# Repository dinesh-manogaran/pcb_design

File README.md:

View this project on [CADLAB.io](https://cadlab.io/project/29153). 

# pcb_design

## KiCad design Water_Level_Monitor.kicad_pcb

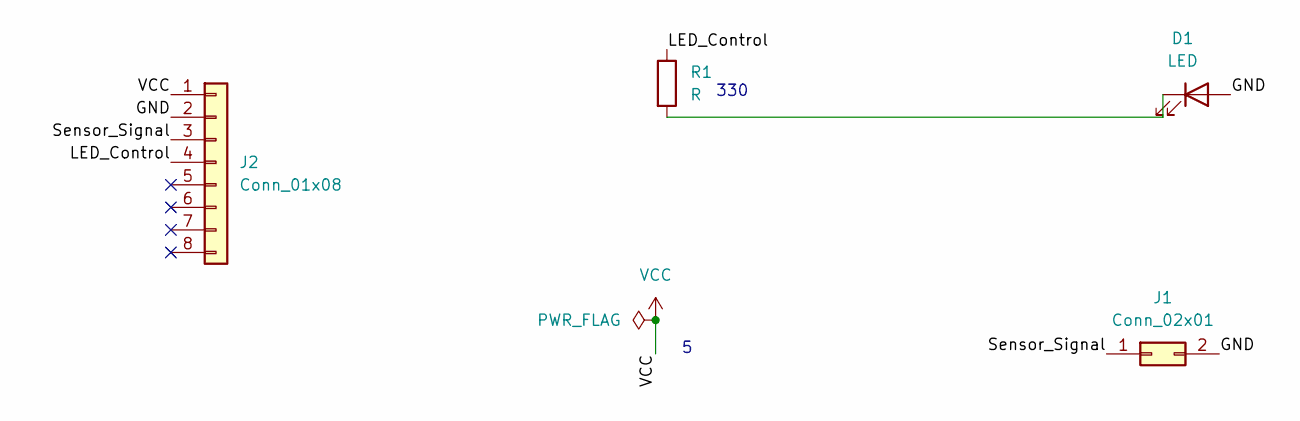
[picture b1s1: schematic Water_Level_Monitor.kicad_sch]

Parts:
D1: LED; LED_D5.0mm
J1: Conn_02x01; PinHeader_1x02_P2.54mm_Vertical
J2: Conn_01x08; PinHeader_1x08_P2.54mm_Vertical
R1: R; R_Axial_DIN0207_L6.3mm_D2.5mm_P7.62mm_Horizontal

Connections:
/GND: D1.2 (A), J1.2, J2.2
/LED_Control: J2.4, R1.1
/Sensor_Signal: J1.1, J2.3
unnamed: D1.1 (K), R1.2
VCC: J2.1

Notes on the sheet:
330

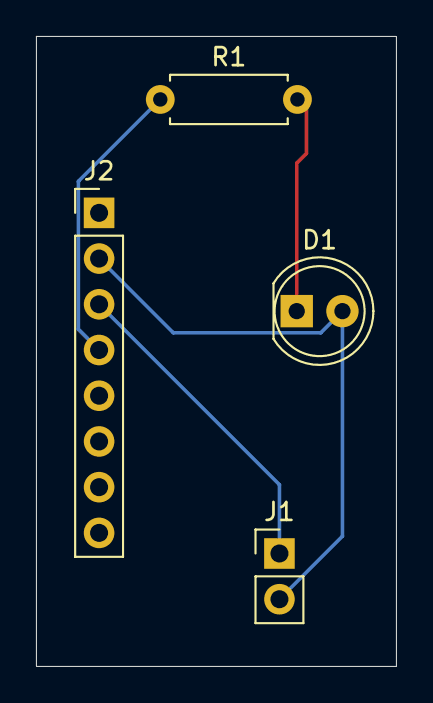
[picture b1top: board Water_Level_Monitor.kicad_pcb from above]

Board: 2 copper layers, 20.0 x 35.0 mm, 4 parts (0 on the bottom side), 4 nets.

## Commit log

2025-04-03 Pcb_design
2025-04-03 Backlink to CADLAB.io has been added.
